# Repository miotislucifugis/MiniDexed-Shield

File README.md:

# MiniDexed-Shield
MiniDexed Shield is compact yet full-featured and highy configurable hardware solution for runnning Minidexed: https://github.com/probonopd/MiniDexed

Minimal parts list and very friendly for DIY novices. Almost entirely through hole components.  (Kalih Choc and Cherry MX keyswitch expander boards have some SMD parts, but still beginner friendly.) 
### Features
1602 LCD

PCM5102A DAC module

encoder w/ switch

2x 1/4" outs for L and R channels.

3.5mm stereo line out jack that can drive headphones.

TRS Serial Midi In and Out via 2x 3.5 jacks

Optional Expander boards provide Master Volume control and user configurable GPIO buttons.   5 button w/ tactile switchs or 4 buttons using the "Choc" or "MX" keyswitch expander boards.

Configurable Audio routing options - Direct out = bypass master volume control,  Mono Summing on 1/4" jacks,  switching 3.5mm out jack disconnects the individual 1/4" outs

More info comming soon

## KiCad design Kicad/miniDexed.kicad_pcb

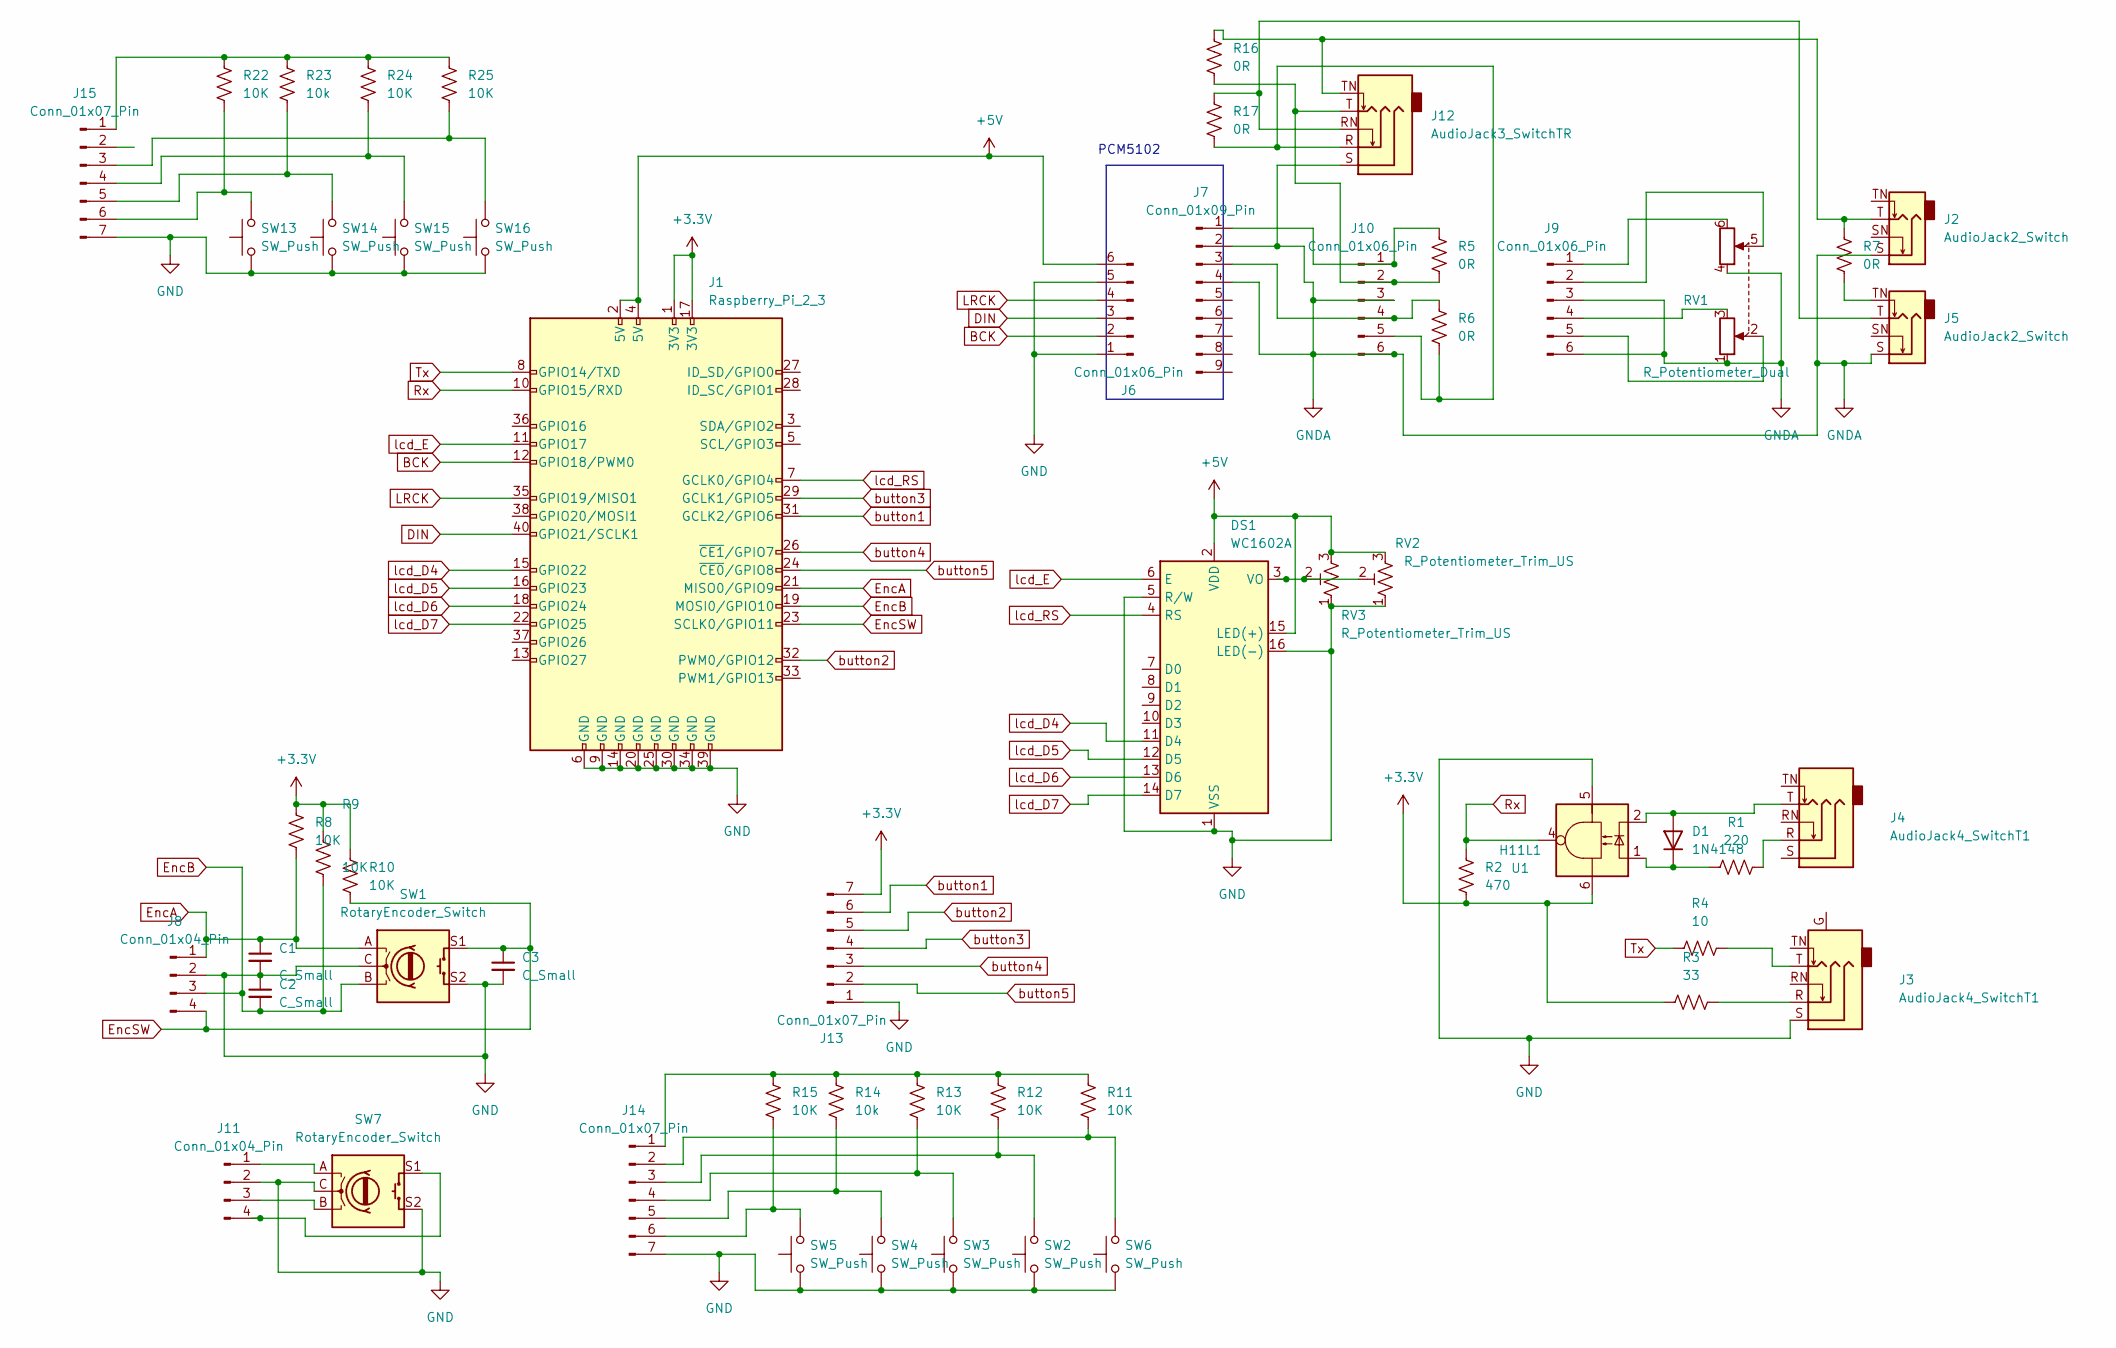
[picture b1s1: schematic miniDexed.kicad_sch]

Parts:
C1, C2, C3: C_Small; C_Disc_D3.0mm_W2.0mm_P2.50mm
D1: 1N4148; D_DO-35_SOD27_P7.62mm_Horizontal
DS1: WC1602A
J1: Raspberry_Pi_2_3; PinHeader_2x20_P2.54mm_Vertical
J2, J5: AudioJack2_Switch; Jack_6.35mm_Neutrik_NMJ6HCD3_Horizontal
J3, J4: AudioJack4_SwitchT1; Jack_3.5mm_CUI_SJ1-3525N_Horizontal
J6, J9, J10: Conn_01x06_Pin; PinHeader_1x06_P2.54mm_Vertical
J7: Conn_01x09_Pin; PinHeader_1x09_P2.54mm_Vertical
J8, J11: Conn_01x04_Pin; PinHeader_1x04_P2.54mm_Vertical
J12: AudioJack3_SwitchTR; Jack_3.5mm_CUI_SJ1-3525N_Horizontal
J13, J14, J15: Conn_01x07_Pin; PinSocket_1x07_P2.54mm_Vertical
R1: 220; R_Axial_DIN0204_L3.6mm_D1.6mm_P7.62mm_Horizontal
R2: 470; R_Axial_DIN0204_L3.6mm_D1.6mm_P7.62mm_Horizontal
R3: 33; R_Axial_DIN0204_L3.6mm_D1.6mm_P7.62mm_Horizontal
R4: 10; R_Axial_DIN0204_L3.6mm_D1.6mm_P7.62mm_Horizontal
R5, R6, R7, R16, R17: 0R; R_0603_1608Metric
R8, R9, R10, R11, R12, R13, R15: 10K; R_Axial_DIN0204_L3.6mm_D1.6mm_P7.62mm_Horizontal
R14: 10k; R_Axial_DIN0204_L3.6mm_D1.6mm_P7.62mm_Horizontal
R22, R24, R25: 10K; R_0603_1608Metric_Pad0.98x0.95mm_HandSolder
R23: 10k; R_0603_1608Metric_Pad0.98x0.95mm_HandSolder
RV1: R_Potentiometer_Dual; Potentiometer_Alpha_RD902F-40-00D_Dual_Vertical
RV2: R_Potentiometer_Trim_US; Potentiometer_Bourns_3296W_Vertical
RV3: R_Potentiometer_Trim_US; Potentiometer_Bourns_3266W_Vertical
SW1, SW7: RotaryEncoder_Switch; RotaryEncoder_Alps_EC11E-Switch_Vertical_H20mm
SW2, SW3, SW4, SW5, SW6: SW_Push; SW_PUSH_6mm
SW13, SW14, SW15, SW16: SW_Push; Kailh_socket_MX
U1: H11L1; DIP-6_W7.62mm_Socket

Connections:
+3.3V: J1.1 (3V3), J1.17 (3V3), J13.7, R2.2, R3.1, R8.1, R9.1, R10.1, U1.6
+5V: DS1.2 (VDD), DS1.15 (LED(+)), J1.2 (5V), J1.4 (5V), J6.6, RV2.3, RV3.3
BCK: J1.12 (GPIO18/PWM0), J6.2
DIN: J1.40 (GPIO21/SCLK1), J6.3
EncA: C1.1, J1.21 (MISO0/GPIO9), J8.1, R8.2, SW1.A
EncB: C2.2, J1.19 (MOSI0/GPIO10), J8.3, R9.2, SW1.B
EncSW: C3.1, J1.23 (SCLK0/GPIO11), J8.4, R10.2, SW1.S1
GNDA: J2.S, J5.S, J7.2, J7.4, J9.3, J9.6, J10.3, J10.6, J12.S, RV1.1, RV1.4
LRCK: J1.35 (GPIO19/MISO1), J6.4
unnamed: D1.2 (A), J4.T, U1.2
unnamed: D1.1 (K), R1.1, U1.1
unnamed: DS1.3 (VO), RV2.2, RV3.2
unnamed: J3.R, R3.2
unnamed: J3.T, R4.2
unnamed: J4.R, R1.2
unnamed: J5.TN, R7.2
unnamed: J9.1, RV1.6
unnamed: J9.2, RV1.5
unnamed: J9.4, RV1.3
unnamed: J9.5, RV1.2
unnamed: J7.1, J10.1, R5.1
unnamed: J10.2, J12.T, R5.2, R16.2
unnamed: J7.3, J10.4, R6.1
unnamed: J10.5, J12.R, R6.2, R17.2
unnamed: J11.1, SW7.A
unnamed: J11.3, SW7.B
unnamed: J11.4, SW7.S1
unnamed: J5.T, J12.RN, R17.1
unnamed: J2.T, J12.TN, R7.1, R16.1
unnamed: J14.1, R11.1, R12.1, R13.1, R14.1, R15.1
unnamed: J14.2, R11.2, SW6.2
unnamed: J14.3, R12.2, SW2.2
unnamed: J14.4, R13.2, SW3.2
unnamed: J14.5, R14.2, SW4.2
unnamed: J14.6, R15.2, SW5.2
unnamed 35: J15.3, R25.2, SW16.2; also elsewhere on the board
unnamed 36: J15.4, R24.2, SW15.2; also elsewhere on the board
unnamed 37: J15.5, R23.2, SW14.2; also elsewhere on the board
unnamed 38: J15.6, R22.2, SW13.2; also elsewhere on the board
Rx: J1.10 (GPIO15/RXD), R2.1, U1.4
Tx: J1.8 (GPIO14/TXD), R4.1
button1: J1.31 (GCLK2/GPIO6), J13.6
button2: J1.32 (PWM0/GPIO12), J13.5
button3: J1.29 (GCLK1/GPIO5), J13.4
button4: J1.26 (~CE1/GPIO7), J13.3
button5: J1.24 (~CE0/GPIO8), J13.2
lcd_D4: DS1.11 (D4), J1.15 (GPIO22)
lcd_D5: DS1.12 (D5), J1.16 (GPIO23)
lcd_D6: DS1.13 (D6), J1.18 (GPIO24)
lcd_D7: DS1.14 (D7), J1.22 (GPIO25)
lcd_E: DS1.6 (E), J1.11 (GPIO17)
lcd_RS: DS1.4 (RS), J1.7 (GCLK0/GPIO4)

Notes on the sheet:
PCM5102

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
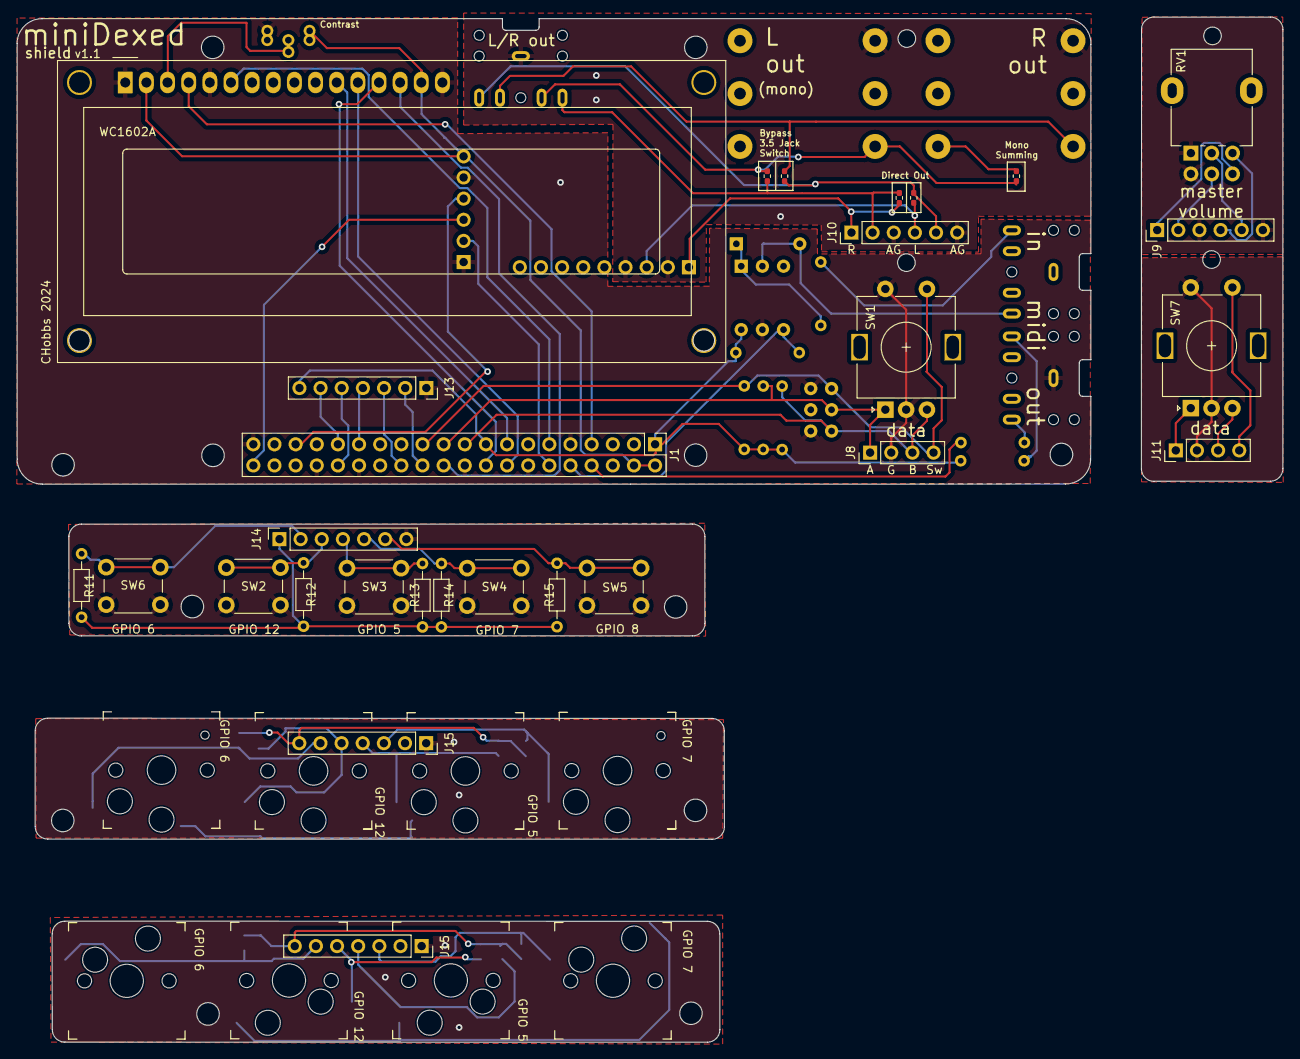
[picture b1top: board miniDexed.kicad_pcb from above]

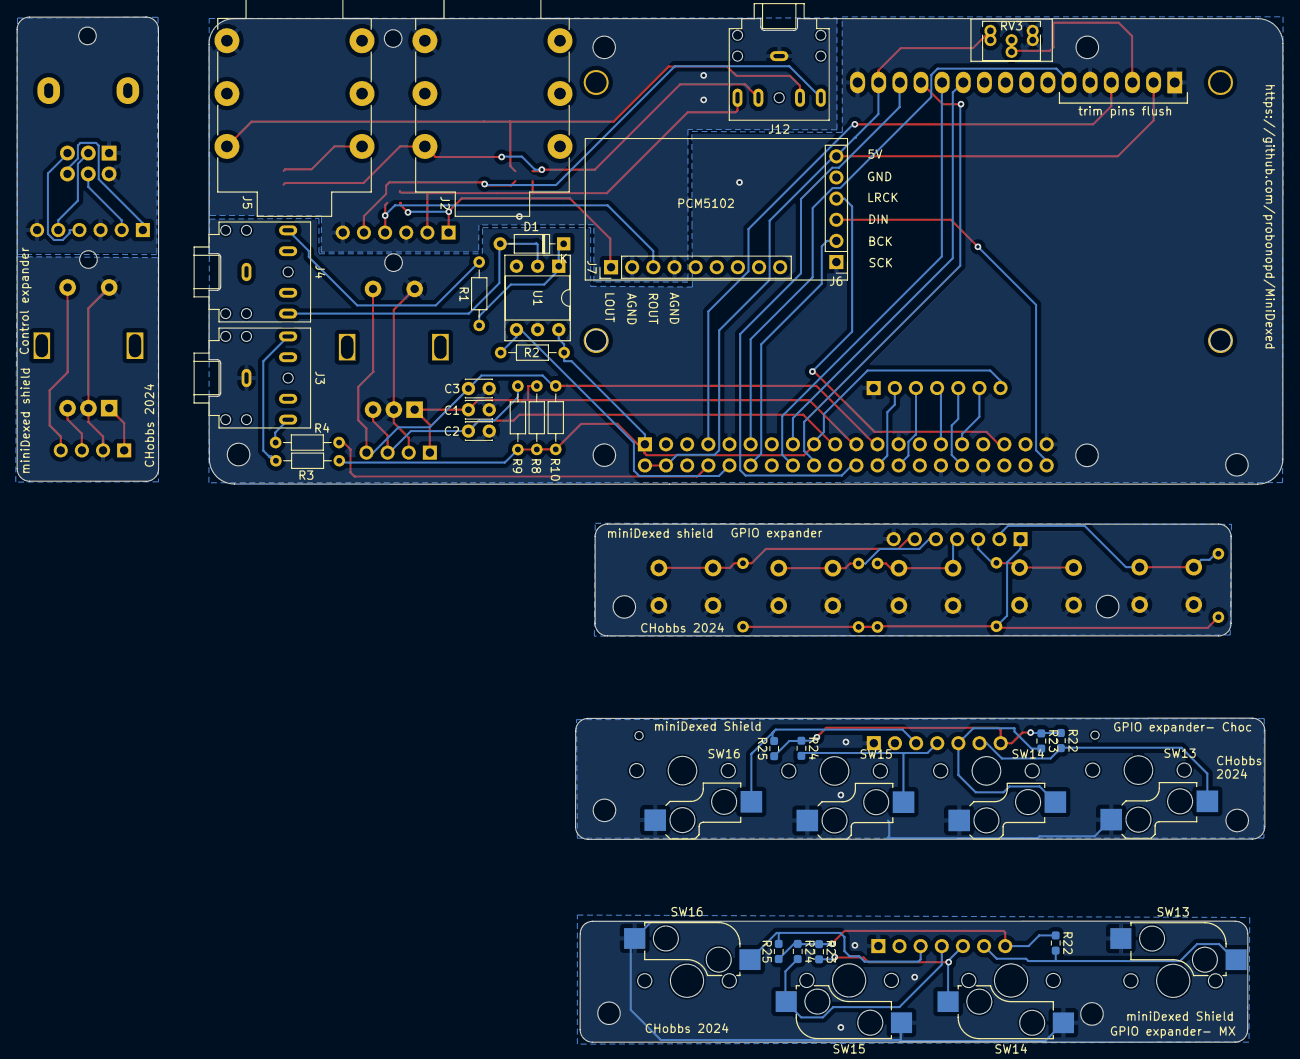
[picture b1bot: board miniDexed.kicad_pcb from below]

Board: 2 copper layers, 152.0 x 123.1 mm, 65 parts (29 on the bottom side), 54 nets.

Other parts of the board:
J15#2: Conn_01x07_Pin; PinSocket_1x07_P2.54mm_Vertical
R22#2, R24#2, R25#2: 10K; R_0603_1608Metric_Pad0.98x0.95mm_HandSolder
R23#2: 10k; R_0603_1608Metric_Pad0.98x0.95mm_HandSolder
SW13#2, SW14#2, SW15#2, SW16#2: SW_Push; Kailh_socket_PG1350

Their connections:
unnamed 35: J15#2.3, R25#2.2, SW16#2.2; also elsewhere on the board
unnamed 36: J15#2.4, R24#2.2, SW15#2.2; also elsewhere on the board
unnamed 37: J15#2.5, R23#2.2, SW14#2.2; also elsewhere on the board
unnamed 38: J15#2.6, R22#2.2, SW13#2.2; also elsewhere on the board

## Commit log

2024-09-03 Rename miniDexed.kicad_pcb to miniDexed_Shield.kicad_pcb
2024-09-03 Rename miniDexed.kicad_sch to miniDexed_Shield.kicad_sch
2024-09-03 Rename miniDexed.kicad_pro to miniDexed_Shield.kicad_pro
2024-09-14 Add files via upload
    fixed some silk screen errors
2024-09-17 Rename IMG_6118.jpg to Photos/IMG_6118.jpg
2024-09-17 Rename IMG_6119.jpg to Photos/IMG_6119.jpg
2024-09-17 Rename IMG_6131.jpg to Photos/IMG_6131.jpg
2024-10-05 Add files via upload
    corrected some minor edge cut errors that prevented .step file generation
2024-10-05 Rename miniDexed.kicad_pcb to miniDexedShield.kicad_pcb
